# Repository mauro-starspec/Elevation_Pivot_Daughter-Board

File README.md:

# Elevation / Pivot - compact controller stack

**P6 compact attempt: two 80 x 130 mm boards.** Active branch:
`compact-80x130`. The complete P5 120 x 200 mm design is preserved on
`custom-controller-stack`, commit `29b4387`, and pushed to GitHub.

| Open in KiCad | Placement and board responsibility |
|---|---|
| [Carrier project](Elevation_Pivot_Daughter-Board.kicad_pro) | Power conversion/protection, brakes, CAN, motor encoders, Modbus and ADC/temperature; five DE9s |
| [Controller project](controller/Elevation_Controller.kicad_pro) | STM32H723, Ethernet/USB/debug, SSI and stepper interfaces; four DE9s |

All 503 footprints are placed on both faces: 258 controller, 245 carrier.
The complete SSI and stepper sheets moved to the controller (92 components).
Moved references gain 1000: e.g. carrier J2 becomes controller J1002.
Components, functional connections and native KiCad BOM metadata are preserved.
The converter architecture is unchanged and remains open for review.

**P6 uses a new stacking pinout. Do not mate P6 with P4/P5 boards.** J30 carries
clean logic and STM32 supplies; J31 carries field supplies and -BATT return.
All 50 contacts and four shared support pairs are checked. Board-face gap is
12 mm, PCB thickness 1.6 mm; tall converters face outward below the carrier.

No routed tracks, vias or copper zones. This demonstrates a compact placement
candidate, not completed routing, cable/enclosure fit or manufacturing release.

- [Current handoff](PROJECT_HANDOFF.md)
- [Assembly and placement notes](assembly/README.md)
- [Exact migration and P6 pinout](assembly/compact_manifest.json)
- [Electrical audit](docs/validation/p6_electrical_results.json)
- [Placement audit](docs/validation/p6_placement_results.json)
- Review images: `docs/reviews/p6/` (top and bottom of each board).

Run `python tools/validate_stack.py` for P6 exports, ERC, connectivity and native
PCB checks. BOM remains in the schematic editor's **Project BOM** field-table
preset. Earlier P4 PDFs and P5 assembly notes describe historical revisions.

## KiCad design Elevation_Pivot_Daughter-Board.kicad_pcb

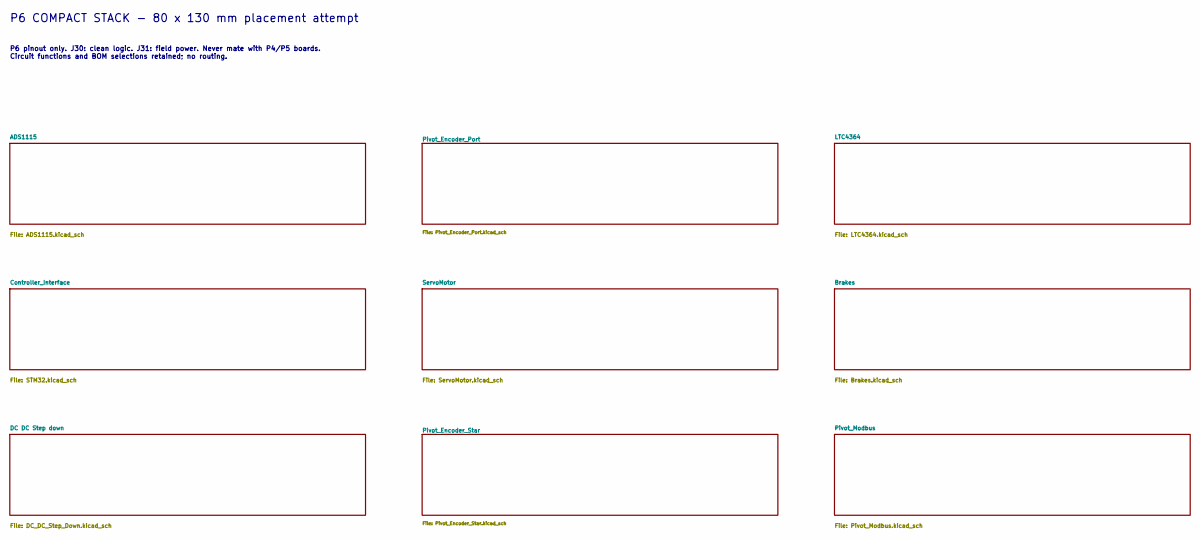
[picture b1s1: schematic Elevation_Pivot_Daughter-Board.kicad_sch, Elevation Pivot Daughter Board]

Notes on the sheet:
P6 COMPACT STACK - 80 x 130 mm placement attempt
P6 pinout only. J30: clean logic. J31: field power. Never mate with P4/P5 boards. Circuit functions and BOM selections retained; no routing.

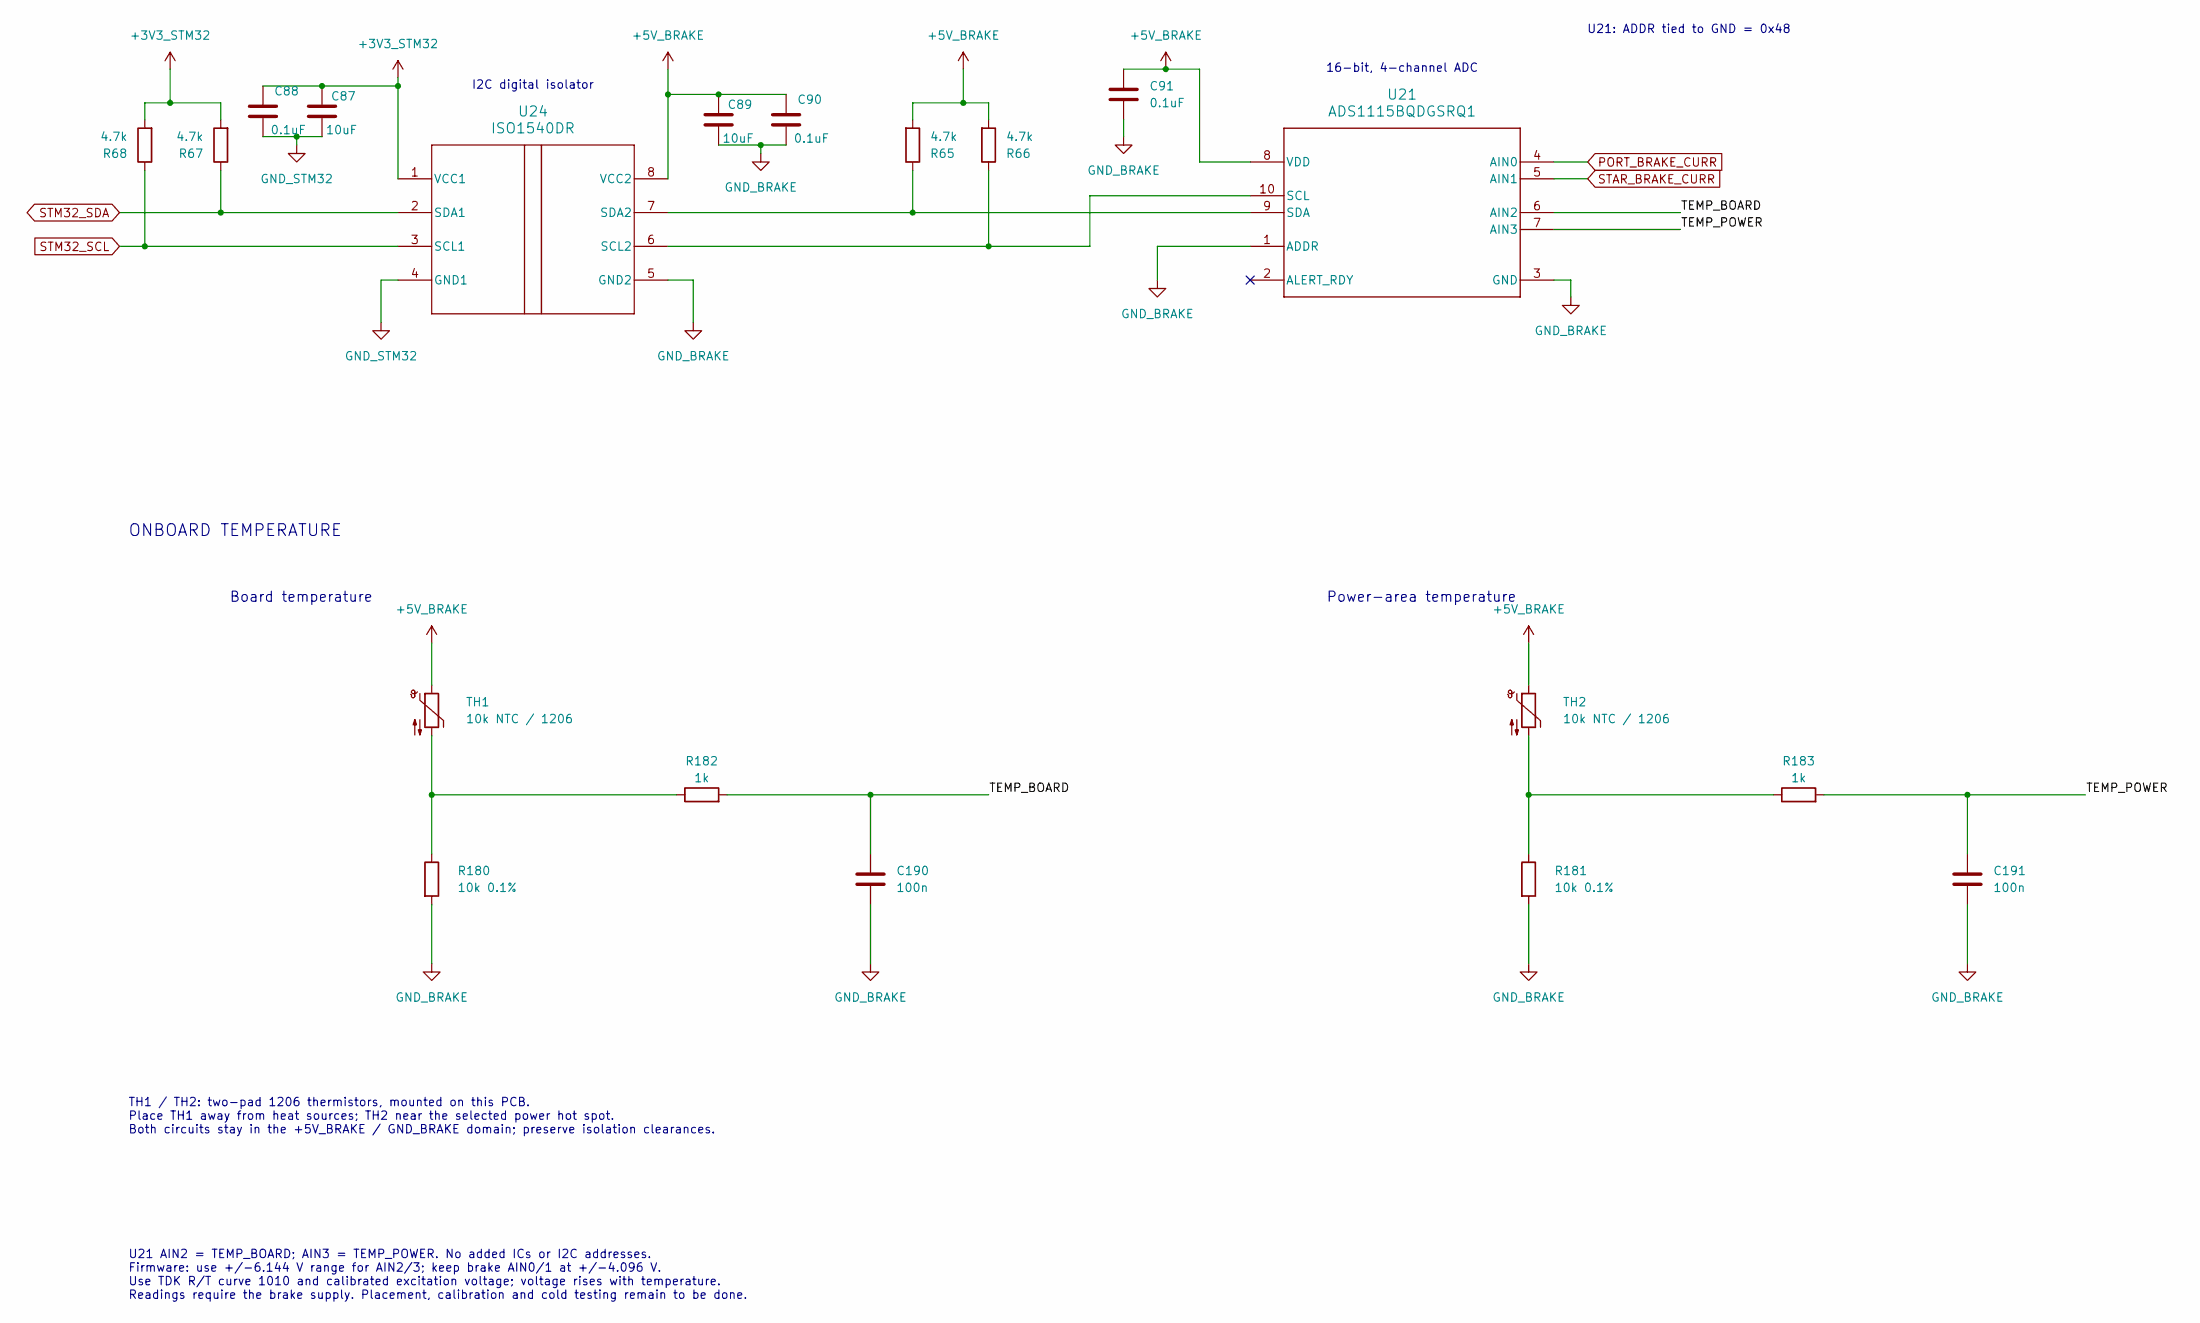
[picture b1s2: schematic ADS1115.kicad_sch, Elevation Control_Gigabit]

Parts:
C87, C89: 10uF; C_1210_3225Metric; MANUFACTURER_PART_NUMBER CL32B106KBJNFNE; LCSC C18739
C88, C90, C91: 0.1uF; C_0805_2012Metric; MANUFACTURER_PART_NUMBER CL21B104KCFNNNE; LCSC C28233
C190, C191: 100n; C_0805_2012Metric; MPN CL21B104KCFNNNE; JLCPCB Status Historical ID; recheck exact part and a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
R65, R66, R67, R68: 4.7k; R_0805_2012Metric; MANUFACTURER_PART_NUMBER RC0805FR-074K7L; LCSC C60816
R180, R181: 10k 0.1%; R_0805_2012Metric; Voltage 150 V maximum working; Tolerance 0.1%; MPN RT0805BRD0710KL; JLCPCB Library UNVERIFIED
R182, R183: 1k; R_0805_2012Metric; MPN RC0805FR-071KL; JLCPCB Status Historical ID; recheck exact part and a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
TH1, TH2: 10k NTC / 1206; R_1206_3216Metric; Tolerance 5% at 25 C; MANUFACTURER_PART_NUMBER B57621C5103J062; JLCPCB Library UNVERIFIED
U21: ADS1115BQDGSRQ1; ADS1115BQDGSRQ1_N; MANUFACTURER_PART_NUMBER ADS1115BQDGSRQ1; LCSC C2868291
U24: ISO1540DR; ISO1540DR_M; MANUFACTURER_PART_NUMBER ISO1540DR; LCSC C179739

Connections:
+3V3_STM32: C87.1, C88.2, R67.2, R68.2, U24.1 (VCC1); also elsewhere on the board
+5V_BRAKE: C89.1, C90.2, C91.1, R65.2, R66.2, TH1.1, TH2.1, U21.8 (VDD), U24.8 (VCC2); also elsewhere on the board
/ADS1115/TEMP_BOARD: C190.1, R182.2, U21.6 (AIN2)
/ADS1115/TEMP_POWER: C191.1, R183.2, U21.7 (AIN3)
GND_BRAKE: C89.2, C90.1, C91.2, C190.2, C191.2, R180.2, R181.2, U21.1 (ADDR), U21.3 (GND), U24.5 (GND2); also elsewhere on the board
GND_STM32: C87.2, C88.1, U24.4 (GND1); also elsewhere on the board
unnamed: R180.1, R182.1, TH1.2
unnamed: R181.1, R183.1, TH2.2
unnamed: R66.1, U21.10 (SCL), U24.6 (SCL2)
unnamed: R65.1, U21.9 (SDA), U24.7 (SDA2)
PORT_BRAKE_CURR: U21.4 (AIN0); also elsewhere on the board
STAR_BRAKE_CURR: U21.5 (AIN1); also elsewhere on the board
STM32_SCL: R68.1, U24.3 (SCL1); also elsewhere on the board
STM32_SDA: R67.1, U24.2 (SDA1); also elsewhere on the board

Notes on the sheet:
16-bit, 4-channel ADC
Board temperature
U21: ADDR tied to GND = 0x48
I2C digital isolator
TH1 / TH2: two-pad 1206 thermistors, mounted on this PCB. Place TH1 away from heat sources; TH2 near the selected power hot spot. Both circuits stay in the +5V_BRAKE / GND_BRAKE domain; preserve isolation clearances.
ONBOARD TEMPERATURE
U21 AIN2 = TEMP_BOARD; AIN3 = TEMP_POWER. No added ICs or I2C addresses. Firmware: use +/-6.144 V range for AIN2/3; keep brake AIN0/1 at +/-4.096 V. Use TDK R/T curve 1010 and calibrated excitation voltage; voltage rises with temperature. Readings require the brake supply. Placement, calibration an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
Power-area temperature

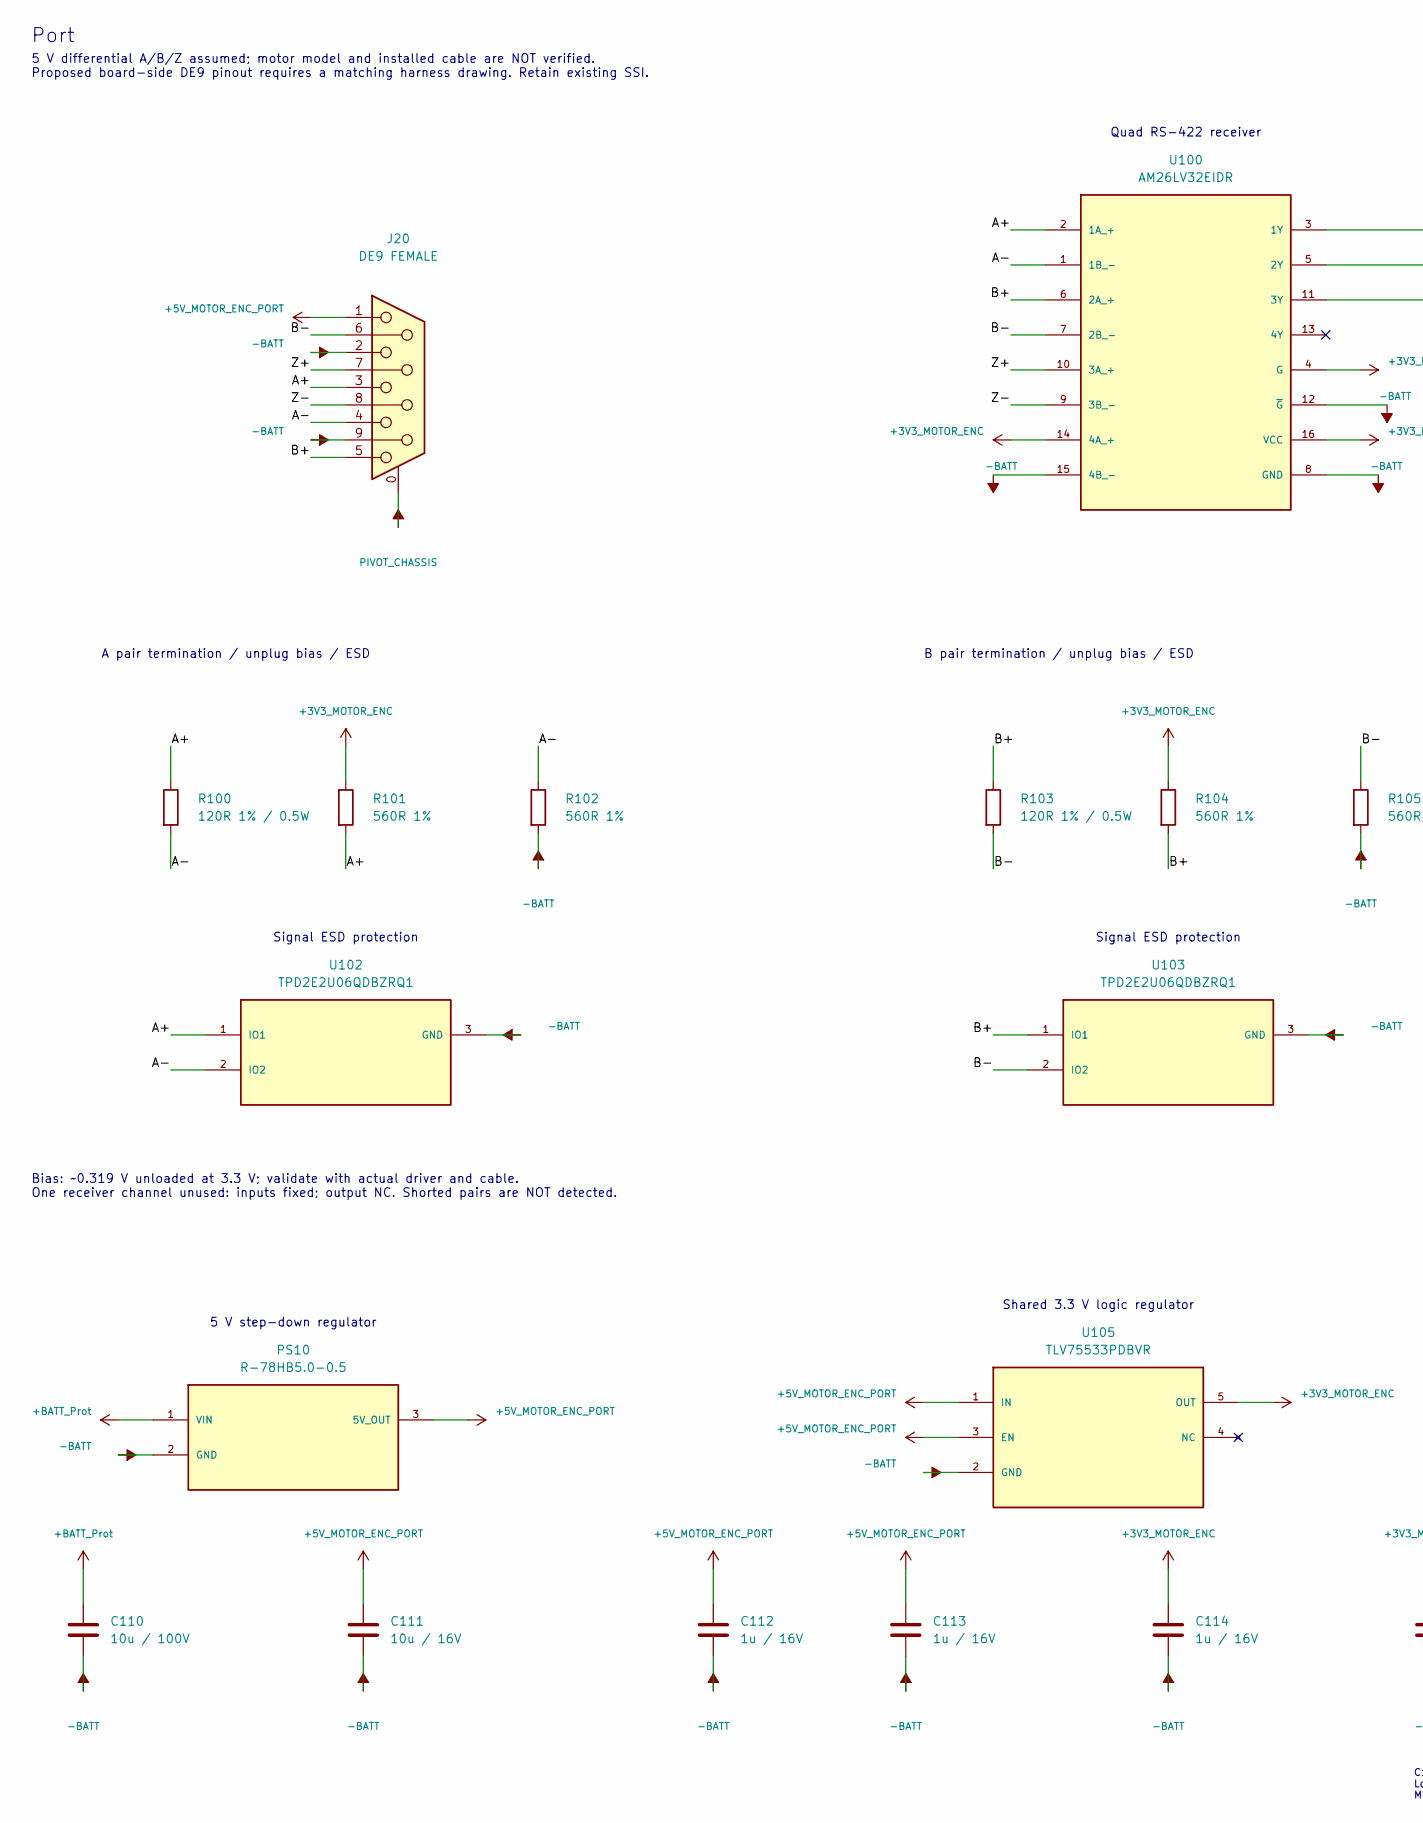
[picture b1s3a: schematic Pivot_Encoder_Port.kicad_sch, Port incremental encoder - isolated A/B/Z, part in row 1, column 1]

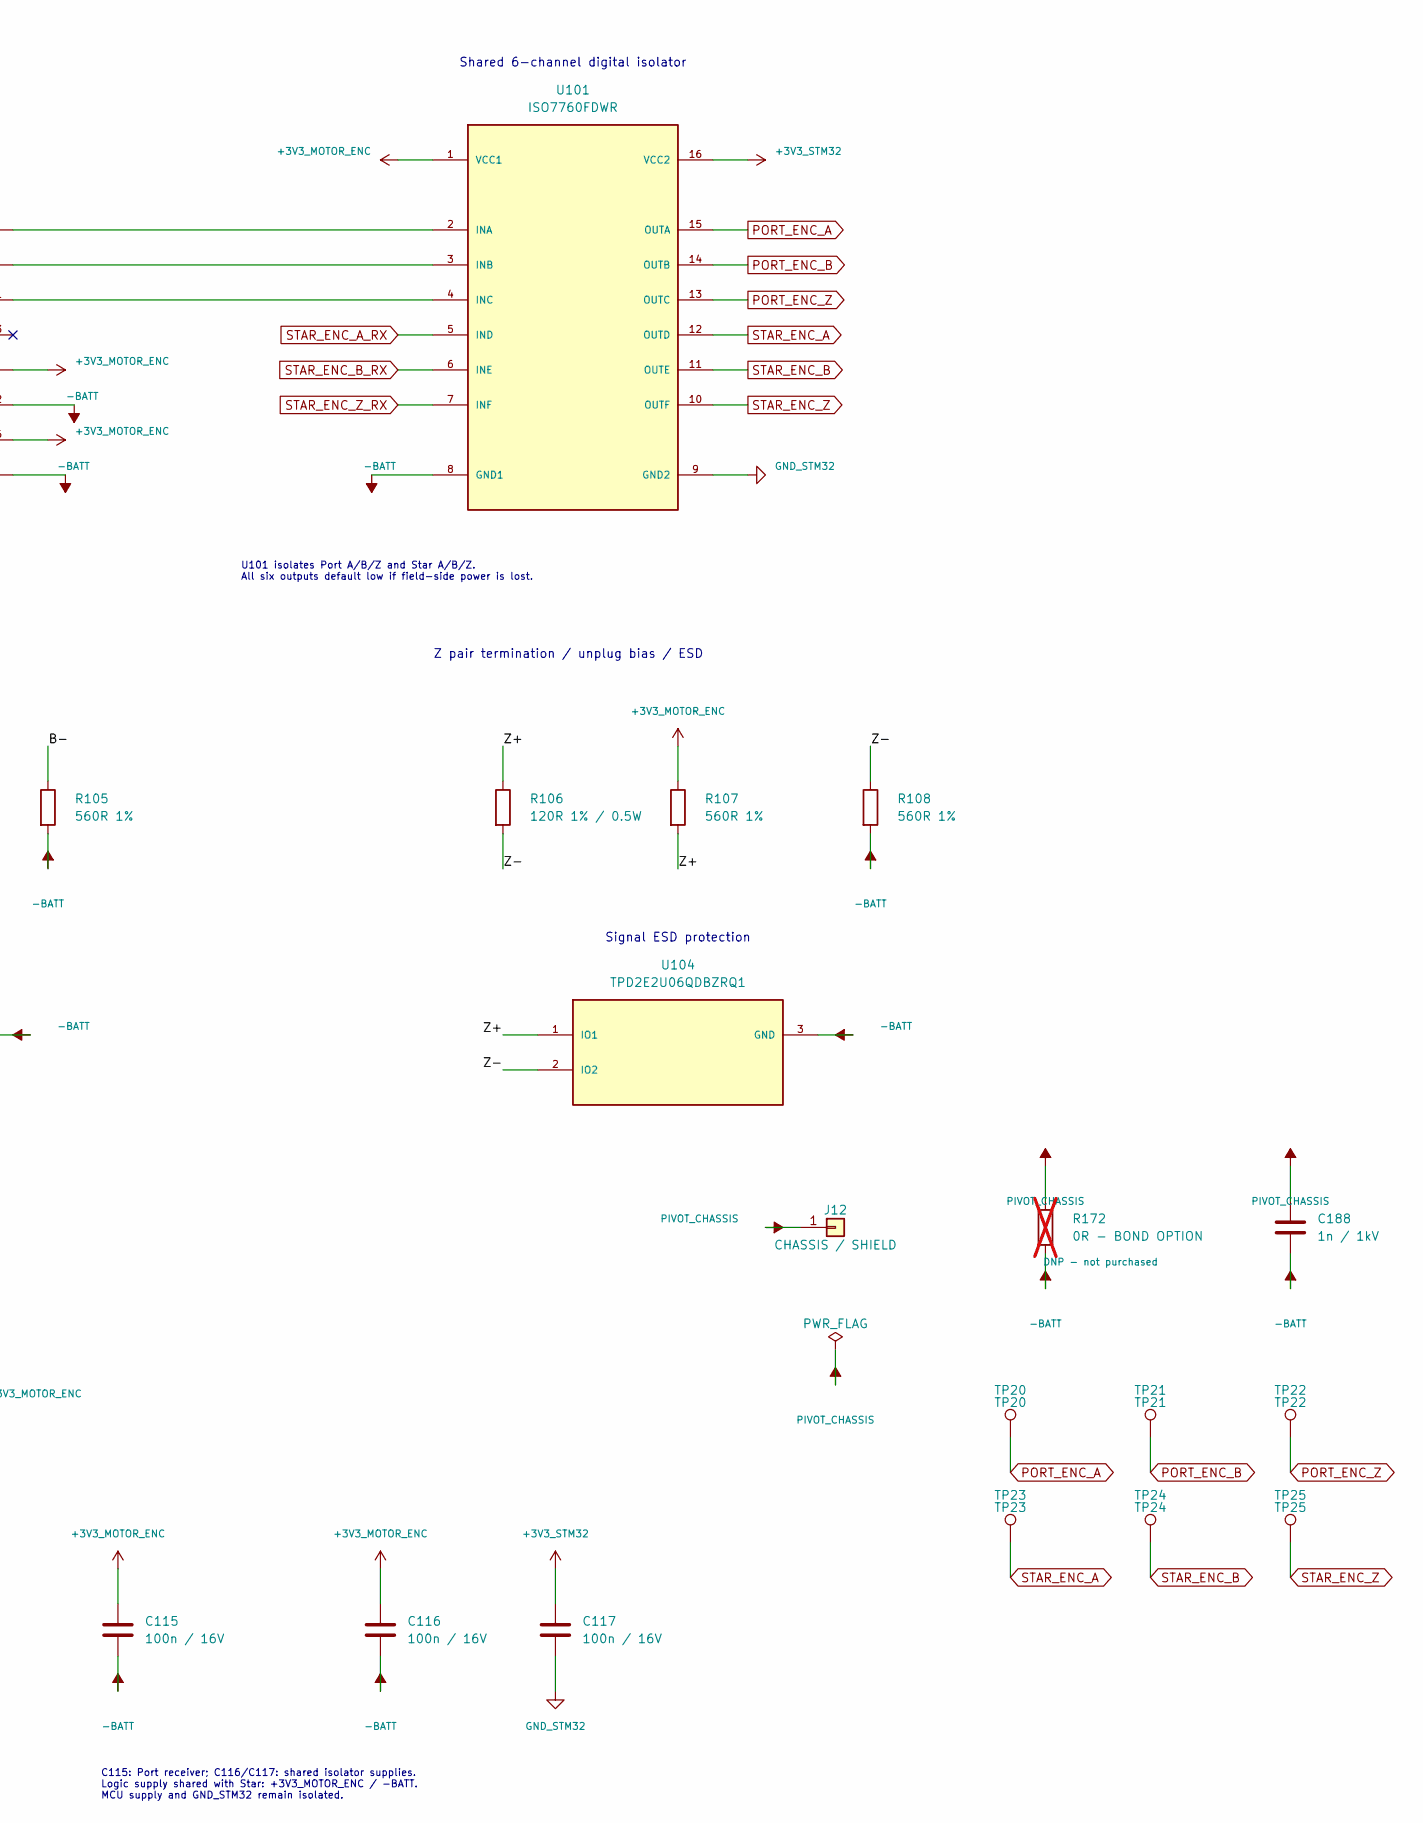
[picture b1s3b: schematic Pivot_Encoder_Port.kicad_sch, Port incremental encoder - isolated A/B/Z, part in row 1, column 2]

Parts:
C110: 10u / 100V; C_1210_3225Metric; Voltage 100 V; Tolerance 10%; MPN CGA6P1X7R2A106K250AC; JLCPCB Status No verified JLCPCB ID; source or consign
C111: 10u / 16V; C_0805_2012Metric; Voltage 16 V; Tolerance 10%; MPN CL21B106KOQNNNE; JLCPCB Status Exact catalog match; stock not verified
C112, C113, C114: 1u / 16V; C_0805_2012Metric; Voltage 25V; MPN C2012X7R1E105K085AB; JLCPCB Status No verified JLCPCB ID; source or consign
C115, C116, C117: 100n / 16V; C_0805_2012Metric; MPN CL21B104KCFNNNE; JLCPCB Status Historical ID; recheck exact part and a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
C188: 1n / 1kV; C_0805_2012Metric; Voltage 1000 V DC; Tolerance 10%; MPN C0805C102KDRACTU; JLCPCB Library UNVERIFIED
J12: CHASSIS / SHIELD; SolderWire-2sqmm_1x01_D2mm_OD3.9mm; MPN N/A; JLCPCB Status N/A
J20: DE9 FEMALE; DSUB-9_Socket_Horizontal_P2.77x2.84mm_EdgePinOffset7.70mm_H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; MPN 5747844-4; JLCPCB Library UNVERIFIED
PS10: R-78HB5.0-0.5; Converter_DCDC_RECOM_R-78HB-0.5_THT; MPN R-78HB5.0-0.5; JLCPCB Status No verified JLCPCB ID; source or consign
R100, R103, R106: 120R 1% / 0.5W; R_1206_3216Metric; Tolerance 1%; MPN ERJ-P08F1200V; JLCPCB Library UNVERIFIED
R101, R102, R104, R105, R107, R108: 560R 1%; R_0805_2012Metric; MPN RC0805FR-07560RL; JLCPCB Status Historical ID; recheck exact part and a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
R172: 0R - BOND OPTION; R_0805_2012Metric; MPN NOT SELECTED - DNP; JLCPCB Status No verified JLCPCB ID; source or consign; not fitted
TP20: TP20; TestPoint_Pad_D1.5mm; MPN N/A; JLCPCB Status N/A
TP21: TP21; TestPoint_Pad_D1.5mm; MPN N/A; JLCPCB Status N/A
TP22: TP22; TestPoint_Pad_D1.5mm; MPN N/A; JLCPCB Status N/A
TP23: TP23; TestPoint_Pad_D1.5mm; MPN N/A; JLCPCB Status N/A
TP24: TP24; TestPoint_Pad_D1.5mm; MPN N/A; JLCPCB Status N/A
TP25: TP25; TestPoint_Pad_D1.5mm; MPN N/A; JLCPCB Status N/A
U100: AM26LV32EIDR; SOIC-16_3.9x9.9mm_P1.27mm; MPN AM26LV32EIDR; JLCPCB Status Exact catalog match; stock not verified
U101: ISO7760FDWR; SOIC-16W_7.5x10.3mm_P1.27mm; MPN ISO7760FDWR; JLCPCB Library UNVERIFIED
U102, U103, U104: TPD2E2U06QDBZRQ1; SOT-23; MPN TPD2E2U06QDBZRQ1; JLCPCB Status Historical ID; recheck exact part and a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
U105: TLV75533PDBVR; SOT-23-5; MPN TLV75533PDBVR; JLCPCB Status Exact catalog match; stock not verified

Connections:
+3V3_MOTOR_ENC: C114.1, C115.1, C116.1, R101.1, R104.1, R107.1, U100.4 (G), U100.14 (4A_+), U100.16 (VCC), U101.1 (VCC1), U105.5 (OUT); also elsewhere on the board
+3V3_STM32: C117.1, U101.16 (VCC2); also elsewhere on the board
+5V_MOTOR_ENC_PORT: C111.1, C112.1, C113.1, J20.1, PS10.3 (5V_OUT), U105.1 (IN), U105.3 (EN)
+BATT_Prot: C110.1, PS10.1 (VIN); also elsewhere on the board
-BATT: C110.2, C111.2, C112.2, C113.2, C114.2, C115.2, C116.2, C188.2, J20.2, J20.9, PS10.2 (GND), R102.2, R105.2, R108.2, R172.2, U100.8 (GND), U100.12 (~G), U100.15 (4B_-), U101.8 (GND1), U102.3 (GND), U103.3 (GND), U104.3 (GND), U105.2 (GND); also elsewhere on the board
/Pivot_Encoder_Port/A+: J20.3, R100.1, R101.2, U100.2 (1A_+), U102.1 (IO1)
/Pivot_Encoder_Port/A-: J20.4, R100.2, R102.1, U100.1 (1B_-), U102.2 (IO2)
/Pivot_Encoder_Port/B+: J20.5, R103.1, R104.2, U100.6 (2A_+), U103.1 (IO1)
/Pivot_Encoder_Port/B-: J20.6, R103.2, R105.1, U100.7 (2B_-), U103.2 (IO2)
/Pivot_Encoder_Port/Z+: J20.7, R106.1, R107.2, U100.10 (3A_+), U104.1 (IO1)
/Pivot_Encoder_Port/Z-: J20.8, R106.2, R108.1, U100.9 (3B_-), U104.2 (IO2)
GND_STM32: C117.2, U101.9 (GND2); also elsewhere on the board
unnamed: U100.3 (1Y), U101.2 (INA)
unnamed: U100.5 (2Y), U101.3 (INB)
unnamed: U100.11 (3Y), U101.4 (INC)
PIVOT_CHASSIS: C188.1, J12.1, J20.0 (PAD), R172.1; also elsewhere on the board
PORT_ENC_A: TP20.1, U101.15 (OUTA); also elsewhere on the board
PORT_ENC_B: TP21.1, U101.14 (OUTB); also elsewhere on the board
PORT_ENC_Z: TP22.1, U101.13 (OUTC); also elsewhere on the board
STAR_ENC_A: TP23.1, U101.12 (OUTD); also elsewhere on the board
STAR_ENC_A_RX: U101.5 (IND); also elsewhere on the board
STAR_ENC_B: TP24.1, U101.11 (OUTE); also elsewhere on the board
STAR_ENC_B_RX: U101.6 (INE); also elsewhere on the board
STAR_ENC_Z: TP25.1, U101.10 (OUTF); also elsewhere on the board
STAR_ENC_Z_RX: U101.7 (INF); also elsewhere on the board

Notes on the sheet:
5 V differential A/B/Z assumed; motor model and installed cable are NOT verified. Proposed board-side DE9 pinout requires a matching harness drawing. Retain existing SSI.
Shared 3.3 V logic regulator
Bias: ~0.319 V unloaded at 3.3 V; validate with actual driver and cable. One receiver channel unused: inputs fixed; output NC. Shorted pairs are NOT detected.
C115: Port receiver; C116/C117: shared isolator supplies. Logic supply shared with Star: +3V3_MOTOR_ENC / -BATT. MCU supply and GND_STM32 remain isolated.
Signal ESD protection
Shared 6-channel digital isolator
Port
Z pair termination / unplug bias / ESD
Quad RS-422 receiver
5 V step-down regulator
B pair termination / unplug bias / ESD
A pair termination / unplug bias / ESD
U101 isolates Port A/B/Z and Star A/B/Z. All six outputs default low if field-side power is lost.

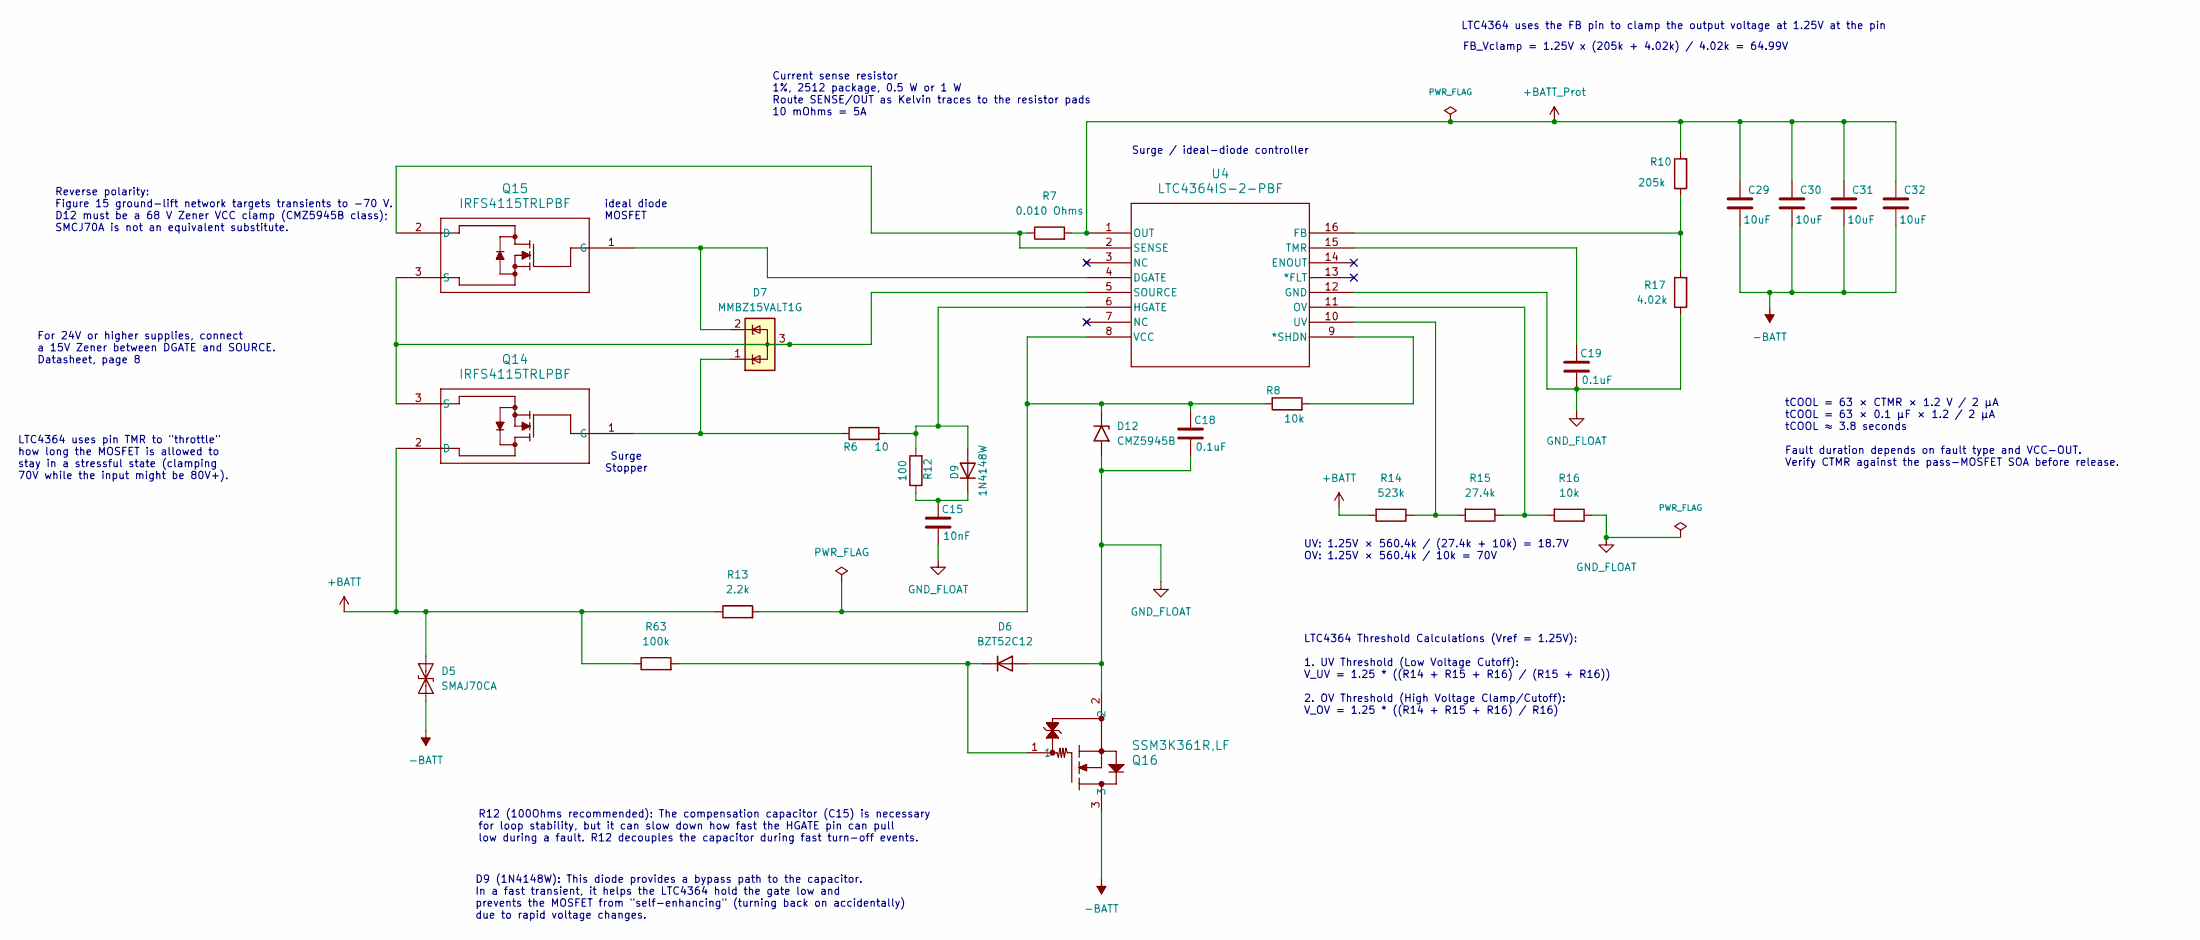
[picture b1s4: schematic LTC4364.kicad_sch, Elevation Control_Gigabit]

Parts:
C15: 10nF; C_0805_2012Metric; MANUFACTURER_PART_NUMBER CL21B103KCANNNC; LCSC C18741
C18: 0.1uF; C_0805_2012Metric; MANUFACTURER_PART_NUMBER CL21B104KCFNNNE; LCSC C28233
C19: 0.1uF; C_1206_3216Metric; MANUFACTURER_PART_NUMBER GCM31C5C1H104FA16L; LCSC C1864297
C29, C30, C31, C32: 10uF; C_2220_5750Metric; MANUFACTURER_PART_NUMBER FS55X106K101EHG; LCSC C153035
D5: SMAJ70CA; DO-214AC_VIS; MANUFACTURER_PART_NUMBER SMAJ70CA-TR; LCSC C132932
D6: BZT52C12; D_SOD-123; MANUFACTURER_PART_NUMBER BZT52C12; LCSC C43491
D7: MMBZ15VALT1G; SOT-23-3; MANUFACTURER_PART_NUMBER MMBZ15VALT1G; LCSC C22582
D9: 1N4148W; D_SOD-123; MANUFACTURER_PART_NUMBER 1N4148W; LCSC C81598
D12: CMZ5945B; D_SMA_Handsoldering; MANUFACTURER_PART_NUMBER CMZ5945B TR13 PBFREE; LCSC C5240502
Q14, Q15: IRFS4115TRLPBF; SUM80090E-GE3; MANUFACTURER_PART_NUMBER IRFS4115TRLPBF; LCSC C53417
Q16: SSM3K361R,LF; SSM3K361R_LXHF; MANUFACTURER_PART_NUMBER SSM3K361R,LF; LCSC C2762698
R6: 10; R_0805_2012Metric; MANUFACTURER_PART_NUMBER RC0805FR-0710RL; LCSC C96347
R7: 0.010 Ohms; R_2512_6332Metric; MANUFACTURER_PART_NUMBER WSL2512R0100FEA18; LCSC C844902
R8, R16: 10k; R_0805_2012Metric; MANUFACTURER_PART_NUMBER RC0805FR-0710KL; LCSC C84376
R10: 205k; R_0805_2012Metric; Tolerance 0.1%; MANUFACTURER_PART_NUMBER RT0805BRD07205KL; LCSC C865289
R12: 100; R_0805_2012Metric; MANUFACTURER_PART_NUMBER RC0805FR-07100RL; LCSC C105577
R13: 2.2k; R_0805_2012Metric; MANUFACTURER_PART_NUMBER RC0805FR-072K2L; LCSC C114561
R14: 523k; R_0805_2012Metric; Tolerance 0.1%; MANUFACTURER_PART_NUMBER RT0805BRD07523KL; LCSC C865545
R15: 27.4k; R_0805_2012Metric; Tolerance 0.1%; MANUFACTURER_PART_NUMBER RT0805BRD0727K4L; LCSC C865348
R17: 4.02k; R_0805_2012Metric; MANUFACTURER_PART_NUMBER PTFR0805Q4K02P9; LCSC C19687933
R63: 100k; R_0805_2012Metric; MANUFACTURER_PART_NUMBER RC0805FR-07100KL; LCSC C96346
U4: LTC4364IS-2-PBF; LTC4364IS-2; MANUFACTURER_PART_NUMBER LTC4364IS-2#PBF; LCSC C688309

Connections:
+BATT: D5.2 (A2), Q14.2 (D), R13.1, R14.2, R63.1; also elsewhere on the board
+BATT_Prot: C29.1, C30.1, C31.1, C32.1, R7.2, R10.2, U4.1 (OUT); also elsewhere on the board
-BATT: C29.2, C30.2, C31.2, C32.2, D5.1 (A1), Q16.3; also elsewhere on the board
GND_FLOAT: C15.2, C18.2, C19.2, D6.2 (A), D12.2 (A2), Q16.2, R16.1, R17.1, U4.12 (GND)
unnamed: D6.1 (K), Q16.1, R63.2
unnamed: D7.3 (A), Q14.3 (S), Q15.3 (S), U4.5 (SOURCE)
unnamed: D9.2 (A), R6.2, R12.2, U4.6 (HGATE)
unnamed: C15.1, D9.1 (K), R12.1
unnamed: C18.1, D12.1 (A1), R8.1, R13.2, U4.8 (VCC)
unnamed: D7.1 (K), Q14.1 (G), R6.1
unnamed: Q15.2 (D), R7.1, U4.2 (SENSE)
unnamed: D7.2 (K), Q15.1 (G), U4.4 (DGATE)
unnamed: R8.2, U4.9 (*SHDN)
unnamed: R10.1, R17.2, U4.16 (FB)
unnamed: R15.1, R16.2, U4.11 (OV)
unnamed: C19.1, U4.15 (TMR)
unnamed: R14.1, R15.2, U4.10 (UV)

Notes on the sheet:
Surge Stopper
D9 (1N4148W): This diode provides a bypass path to the capacitor. In a fast transient, it helps the LTC4364 hold the gate low and prevents the MOSFET from "self-enhancing" (turning back on accidentally) due to rapid voltage changes.
FB_Vclamp = 1.25V x (205k + 4.02k) / 4.02k = 64.99V
For 24V or higher supplies, connect a 15V Zener between DGATE and SOURCE. Datasheet, page 8
tCOOL = 63 × CTMR × 1.2 V / 2 µA tCOOL = 63 × 0.1 µF × 1.2 / 2 µA tCOOL ≈ 3.8 seconds Fault duration depends on fault type and VCC-OUT. Verify CTMR against the pass-MOSFET SOA before release.
LTC4364 Threshold Calculations (Vref = 1.25V): 1. UV Threshold (Low Voltage Cutoff): V_UV = 1.25 * ((R14 + R15 + R16) / (R15 + R16)) 2. OV Threshold (High Voltage Clamp/Cutoff): V_OV = 1.25 * ((R14 + R15 + R16) / R16)
LTC4364 uses the FB pin to clamp the output voltage at 1.25V at the pin
R12 (100Ohms recommended): The compensation capacitor (C15) is necessary for loop stability, but it can slow down how fast the HGATE pin can pull low during a fault. R12 decouples the capacitor during fast turn-off events.
Surge / ideal-diode controller
Current sense resistor 1%, 2512 package, 0.5 W or 1 W Route SENSE/OUT as Kelvin traces to the resistor pads 10 mOhms = 5A
UV: 1.25V × 560.4k / (27.4k + 10k) = 18.7V OV: 1.25V × 560.4k / 10k = 70V
Reverse polarity: Figure 15 ground-lift network targets transients to -70 V. D12 must be a 68 V Zener VCC clamp (CMZ5945B class); SMCJ70A is not an equivalent substitute.
LTC4364 uses pin TMR to "throttle" how long the MOSFET is allowed to stay in a stressful state (clamping 70V while the input might be 80V+).
ideal diode MOSFET

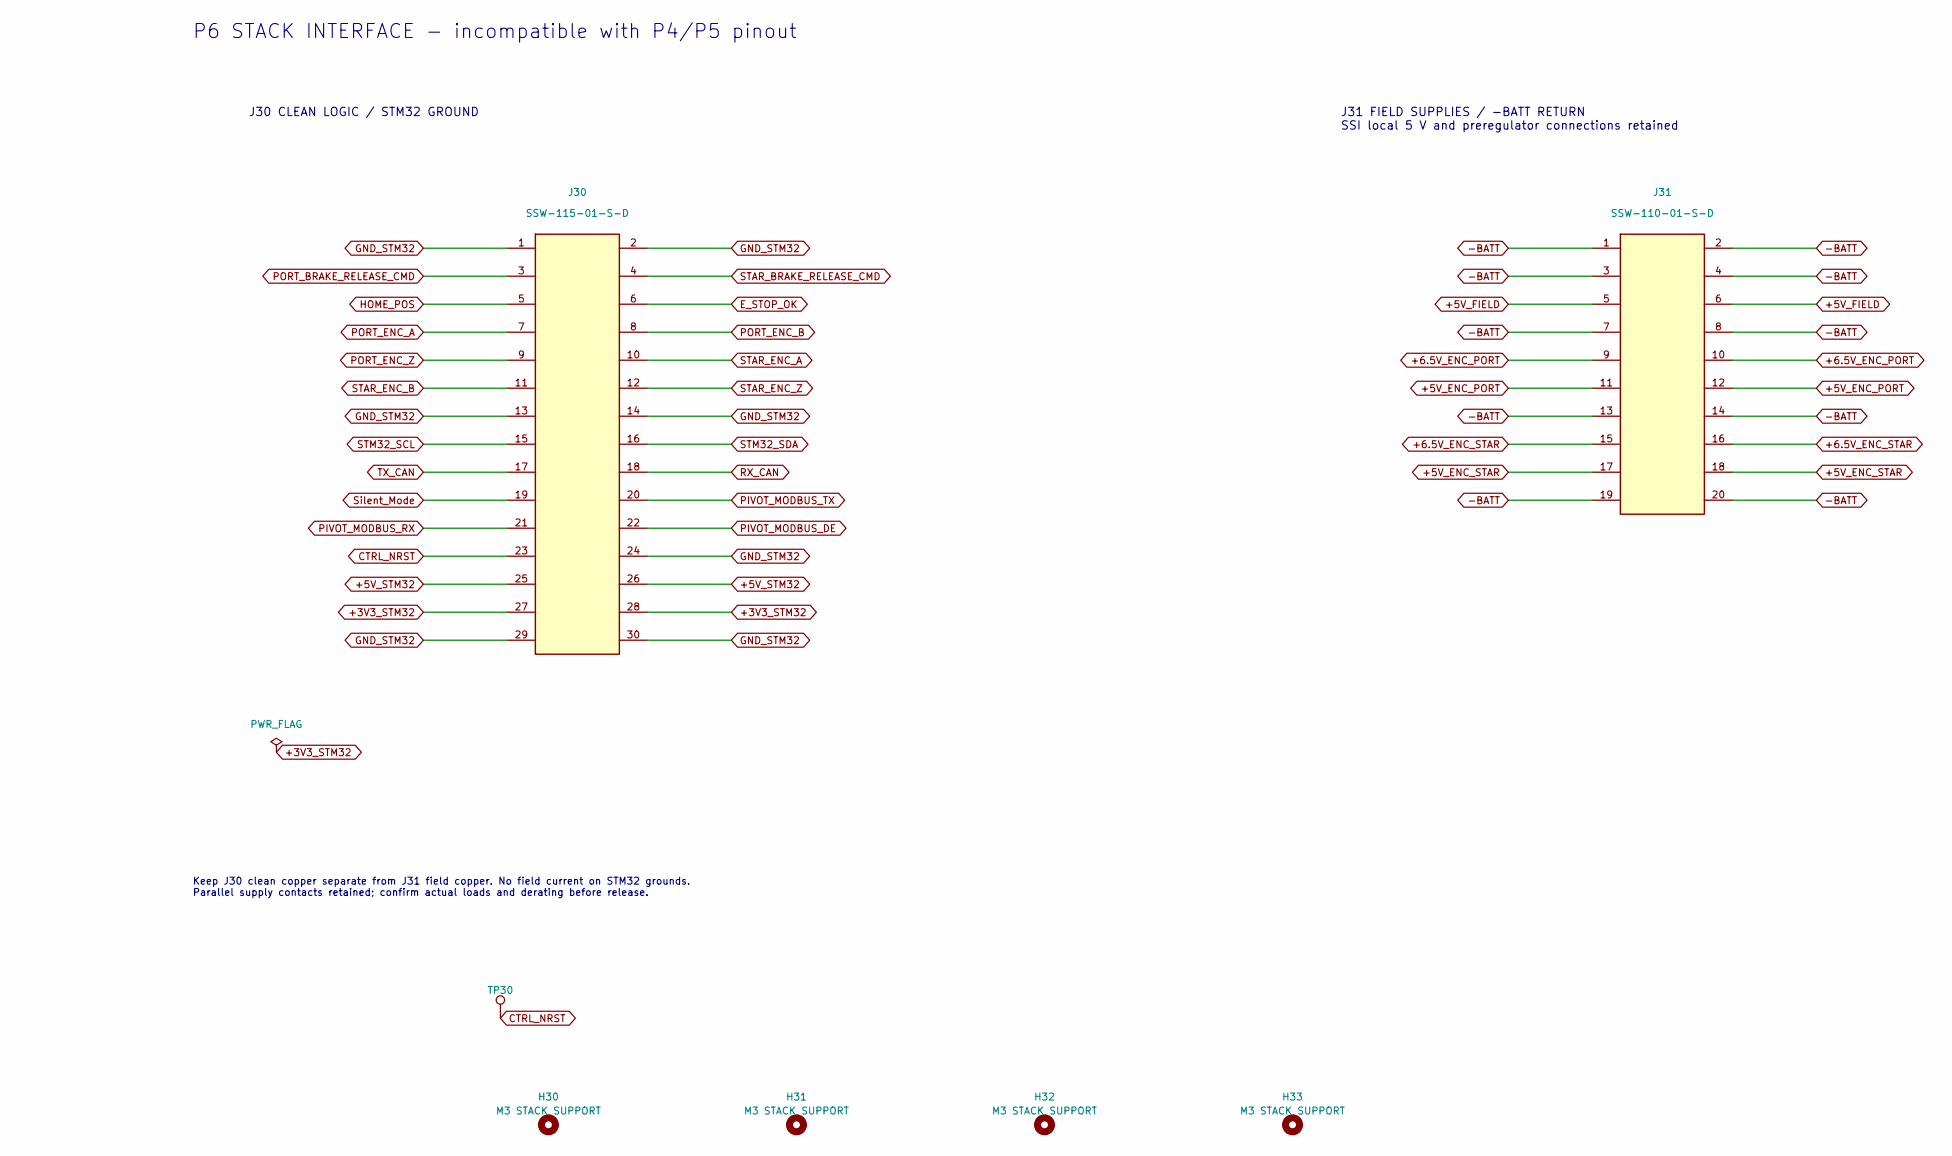
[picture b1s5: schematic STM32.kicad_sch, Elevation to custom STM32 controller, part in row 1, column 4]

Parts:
H5, H6, H7, H8: MountingHole; MountingHole_3.5mm_Pad_TopBottom; MANUFACTURER_PART_NUMBER N/A; LCSC N/A
H30, H31, H32, H33: M3 STACK SUPPORT; MountingHole_3.2mm_M3; MPN N/A; JLCPCB Status N/A
J30: SSW-115-01-S-D; Samtec_SSW-115-01-S-D; MPN SSW-115-01-S-D; JLCPCB Status No verified JLCPCB ID; source or consign
J31: SSW-110-01-S-D; Samtec_SSW-110-01-S-D; MPN SSW-110-01-S-D; JLCPCB Status No verified JLCPCB ID; source or consign
TP30: CTRL_NRST; TestPoint_Pad_D1.5mm; MPN N/A; JLCPCB Status N/A

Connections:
+3V3_STM32: J30.27, J30.28; also elsewhere on the board
+5V_ENC_PORT: J31.11, J31.12; also elsewhere on the board
+5V_ENC_STAR: J31.17, J31.18; also elsewhere on the board
+5V_FIELD: J31.5, J31.6; also elsewhere on the board
+5V_STM32: J30.25, J30.26; also elsewhere on the board
+6.5V_ENC_PORT: J31.9, J31.10; also elsewhere on the board
+6.5V_ENC_STAR: J31.15, J31.16; also elsewhere on the board
-BATT: J31.1, J31.2, J31.3, J31.4, J31.7, J31.8, J31.13, J31.14, J31.19, J31.20; also elsewhere on the board
CTRL_NRST: J30.23, TP30.1
E_STOP_OK: J30.6; also elsewhere on the board
GND_STM32: J30.1, J30.2, J30.13, J30.14, J30.24, J30.29, J30.30; also elsewhere on the board
HOME_POS: J30.5; also elsewhere on the board
PIVOT_MODBUS_DE: J30.22; also elsewhere on the board
PIVOT_MODBUS_RX: J30.21; also elsewhere on the board
PIVOT_MODBUS_TX: J30.20; also elsewhere on the board
PORT_BRAKE_RELEASE_CMD: J30.3; also elsewhere on the board
PORT_ENC_A: J30.7; also elsewhere on the board
PORT_ENC_B: J30.8; also elsewhere on the board
PORT_ENC_Z: J30.9; also elsewhere on the board
RX_CAN: J30.18; also elsewhere on the board
STAR_BRAKE_RELEASE_CMD: J30.4; also elsewhere on the board
STAR_ENC_A: J30.10; also elsewhere on the board
STAR_ENC_B: J30.11; also elsewhere on the board
STAR_ENC_Z: J30.12; also elsewhere on the board
STM32_SCL: J30.15; also elsewhere on the board
STM32_SDA: J30.16; also elsewhere on the board
Silent_Mode: J30.19; also elsewhere on the board
TX_CAN: J30.17; also elsewhere on the board

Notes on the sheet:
P6 STACK INTERFACE - incompatible with P4/P5 pinout
J30 CLEAN LOGIC / STM32 GROUND
J31 FIELD SUPPLIES / -BATT RETURN SSI local 5 V and preregulator connections retained
Keep J30 clean copper separate from J31 field copper. No field current on STM32 grounds. Parallel supply contacts retained; confirm actual loads and derating before release.
